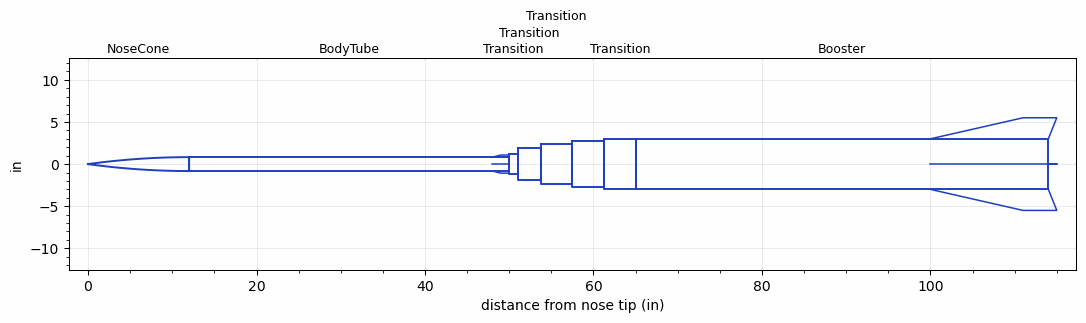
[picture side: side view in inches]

<RASAeroDocument>
 <FileVersion>2</FileVersion>
 <RocketDesign>
  <NoseCone>
   <Length>12</Length>
   <Diameter>1.65</Diameter>
   <Shape>Tangent Ogive</Shape>
   <Location>0</Location>
  </NoseCone>
  <BodyTube>
   <Length>38</Length>
   <Diameter>1.65</Diameter>
   <Location>12</Location>
   <Fin>
    <Count>4</Count>
    <Chord>2</Chord>
    <Span>0.25</Span>
    <SweepDistance>1</SweepDistance>
    <TipChord>1</TipChord>
    <Thickness>0.1</Thickness>
    <LERadius>0.06</LERadius>
    <Location>2</Location>
    <AirfoilSection>Hexagonal</AirfoilSection>
    <FX1>0.3</FX1>
    <FX3>0.3</FX3>
   </Fin>
  </BodyTube>
  <Transition>
   <Length>1</Length>
   <Diameter>2.45</Diameter>
   <Location>50</Location>
   <RearDiameter>2.45</RearDiameter>
  </Transition>
  <Transition>
   <Length>2.75</Length>
   <Diameter>3.75</Diameter>
   <Location>51</Location>
   <RearDiameter>3.75</RearDiameter>
  </Transition>
  <Transition>
   <Length>3.75</Length>
   <Diameter>4.7</Diameter>
   <Location>53.75</Location>
   <RearDiameter>4.7</RearDiameter>
  </Transition>
  <Transition>
   <Length>3.75</Length>
   <Diameter>5.5</Diameter>
   <Location>57.5</Location>
   <RearDiameter>5.5</RearDiameter>
  </Transition>
  <Transition>
   <Length>3.75</Length>
   <Diameter>6</Diameter>
   <Location>61.25</Location>
   <RearDiameter>6</RearDiameter>
  </Transition>
  <Booster>
   <Length>49</Length>
   <Diameter>6</Diameter>
   <InsideDiameter>6</InsideDiameter>
   <Location>65</Location>
   <ShoulderLength>0</ShoulderLength>
   <Fin>
    <Count>4</Count>
    <Chord>14</Chord>
    <Span>2.5</Span>
    <SweepDistance>11</SweepDistance>
    <TipChord>4</TipChord>
    <Thickness>0.118</Thickness>
    <Location>14</Location>
    <AirfoilSection>Square</AirfoilSection>
   </Fin>
  </Booster>
  <Surface>Rough Camouflage Paint</Surface>
  <ModifiedBarrowman>False</ModifiedBarrowman>
  <Turbulence>True</Turbulence>
  <UseBooster1>False</UseBooster1>
  <UseBooster2>False</UseBooster2>
 </RocketDesign>
 <LaunchSite>
  <Altitude>0</Altitude>
  <Pressure>0</Pressure>
  <RodAngle>0</RodAngle>
  <RodLength>4</RodLength>
  <Temperature>74</Temperature>
  <WindSpeed>0</WindSpeed>
 </LaunchSite>
 <Recovery>
  <Altitude1>1000</Altitude1>
  <Altitude2>1000</Altitude2>
  <DeviceType1>Parachute</DeviceType1>
  <DeviceType2>Parachute</DeviceType2>
  <Event1>True</Event1>
  <Event2>True</Event2>
  <Size1>159</Size1>
  <Size2>289</Size2>
  <EventType1>Apogee</EventType1>
  <EventType2>Apogee</EventType2>
  <CD1>0.75</CD1>
  <CD2>0.75</CD2>
 </Recovery>
 <SimulationList>
  <Simulation>
   <SustainerEngine>Dart  (NoThrust)</SustainerEngine>
   <SustainerLaunchWt>0</SustainerLaunchWt>
   <SustainerCG>0</SustainerCG>
   <SustainerIgnitionDelay>0</SustainerIgnitionDelay>
   <Booster1Engine>O5615  (TRT)</Booster1Engine>
   <Booster1SeparationDelay>0</Booster1SeparationDelay>
   <Booster1IgnitionDelay>0</Booster1IgnitionDelay>
   <IncludeBooster1>False</IncludeBooster1>
   <Booster2Delay>0</Booster2Delay>
   <IncludeBooster2>False</IncludeBooster2>
  </Simulation>
  <Simulation>
   <SustainerEngine>Dart  (NoThrust)</SustainerEngine>
   <SustainerLaunchWt>12.29</SustainerLaunchWt>
   <SustainerCG>8.91</SustainerCG>
   <SustainerIgnitionDelay>0</SustainerIgnitionDelay>
   <Booster1Engine>O5615  (TRT)</Booster1Engine>
   <Booster1LaunchWt>52.98</Booster1LaunchWt>
   <Booster1SeparationDelay>0.3</Booster1SeparationDelay>
   <Booster1IgnitionDelay>0</Booster1IgnitionDelay>
   <Booster1CG>46.91</Booster1CG>
   <Booster1NozzleDiameter>5.843</Booster1NozzleDiameter>
   <IncludeBooster1>True</IncludeBooster1>
   <Booster2Delay>0</Booster2Delay>
   <IncludeBooster2>False</IncludeBooster2>
   <TimetoApogee>59.29729</TimetoApogee>
   <MaxAltitude>84005.38</MaxAltitude>
   <MaxVelocity>5992.188</MaxVelocity>
   <OptimumWt>12.29</OptimumWt>
   <OptimumMaxAlt>12.29</OptimumMaxAlt>
  </Simulation>
 </SimulationList>
</RASAeroDocument>
